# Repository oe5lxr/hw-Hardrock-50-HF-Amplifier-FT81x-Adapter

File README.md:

Hardrock-50-HF-Amplifier-FT81x-Adapter
======================================
This adapter allows to control the [Hardrock-50 HF amplifier](https://www.hobbypcb.com/index.php/products/hf-radio/hardrock-50-hf-power-amp) with the popular QRP radio Yaesu [FT-817/817ND/818](https://oe5lxr.at/yaesu-ft-817nd-ultimate-guide/).

Copyright © Alexander Entinger ([OE5LXR](https://oe5lxr.at/)) and Bernhard Mayer ([DL1MAB](https://twitter.com/generation_make)).

Order kit via [Aisler](https://aisler.net/p/WRVRYMXA). In addition to the kit you need a Mini-DIN-8 Male/Male cable.

**Blogpost**: [How to interface your Yaesu FT-817ND/FT-818 radio with a Hardrock-50 HF amplifier
](https://oe5lxr.at/yaesu-ft-817nd-hardrock-interface/).

<p align="center">
  
</p>

## PCB (Top/Bottom)
<p align="center">

</p>

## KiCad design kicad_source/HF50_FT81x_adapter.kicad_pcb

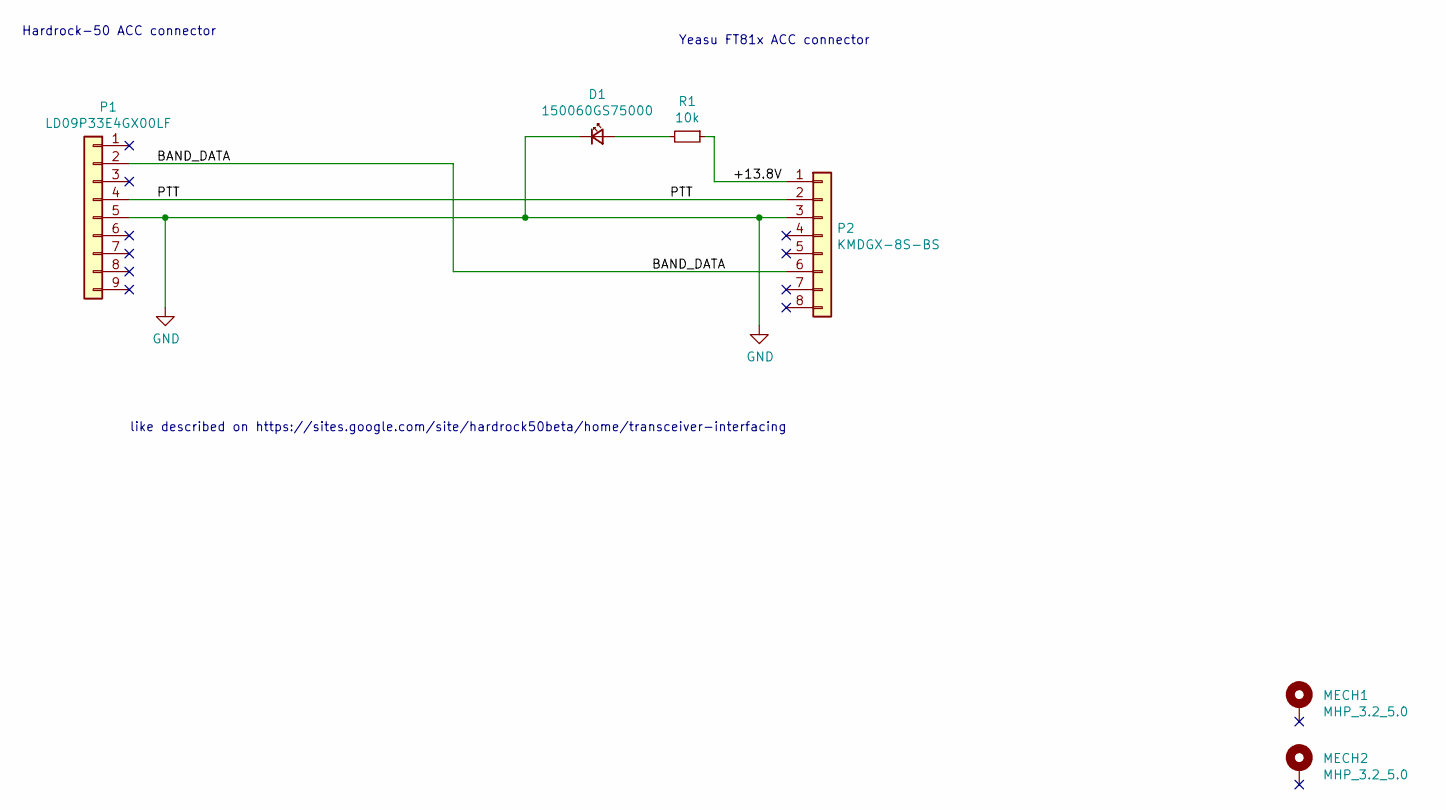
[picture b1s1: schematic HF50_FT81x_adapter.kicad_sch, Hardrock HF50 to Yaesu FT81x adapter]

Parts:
D1: 150060GS75000; LED_D3.0mm
MECH1, MECH2: MHP_3.2_5.0
P1: LD09P33E4GX00LF; DSUB-9_Male_Horizontal_P2.77x2.84mm_EdgePinOffset7.70mm_Hou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
P2: KMDGX-8S-BS; MiniDIN_8
R1: 10k; R_Axial_DIN0207_L6.3mm_D2.5mm_P7.62mm_Horizontal

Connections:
/+13.8V: P2.1, R1.1
/BAND_DATA: P1.2, P2.6
/PTT: P1.4, P2.2
GND: D1.1 (K), P1.5, P2.3
unnamed: D1.2 (A), R1.2

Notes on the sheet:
Yeasu FT81x ACC connector
like described on https://sites.google.com/site/hardrock50beta/home/transceiver-interfacing
Hardrock-50 ACC connector

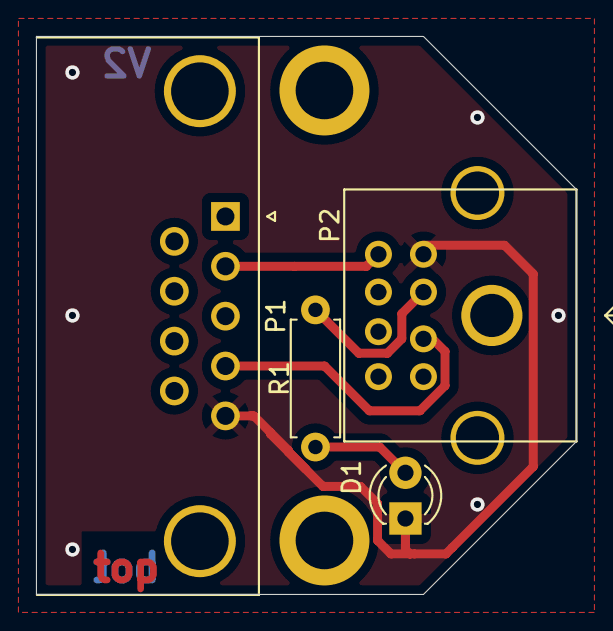
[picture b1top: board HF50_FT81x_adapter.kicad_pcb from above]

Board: 2 copper layers, 30.0 x 31.0 mm, 6 parts (0 on the bottom side), 5 nets.

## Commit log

2021-05-13 started kicad project
2021-05-13 made layout
2021-05-13 added pdf schematic
2021-05-13 added images
2021-05-20 added LED
2021-05-20 added mounting holes
2021-05-20 updated BOM and images, added link to aisler
2021-05-28 Simplifying README.
2021-05-28 Replace standard with horizontal logo.
2021-06-15 Document required cable (Mini-DIN-8 Male/Male)
2021-11-17 Add link to blog post.
2023-04-08 updated to Kicad 6
2023-04-08 switched to THT parts
2023-04-08 updated images and schematic pdf
